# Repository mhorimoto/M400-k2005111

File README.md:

# 音声切り替え装置 (A26)
# K2005111

# 要求するHardware

- Arduino Nano V3
- 8ch Relay module
- I2C LCD 1602A (Address:0x27)

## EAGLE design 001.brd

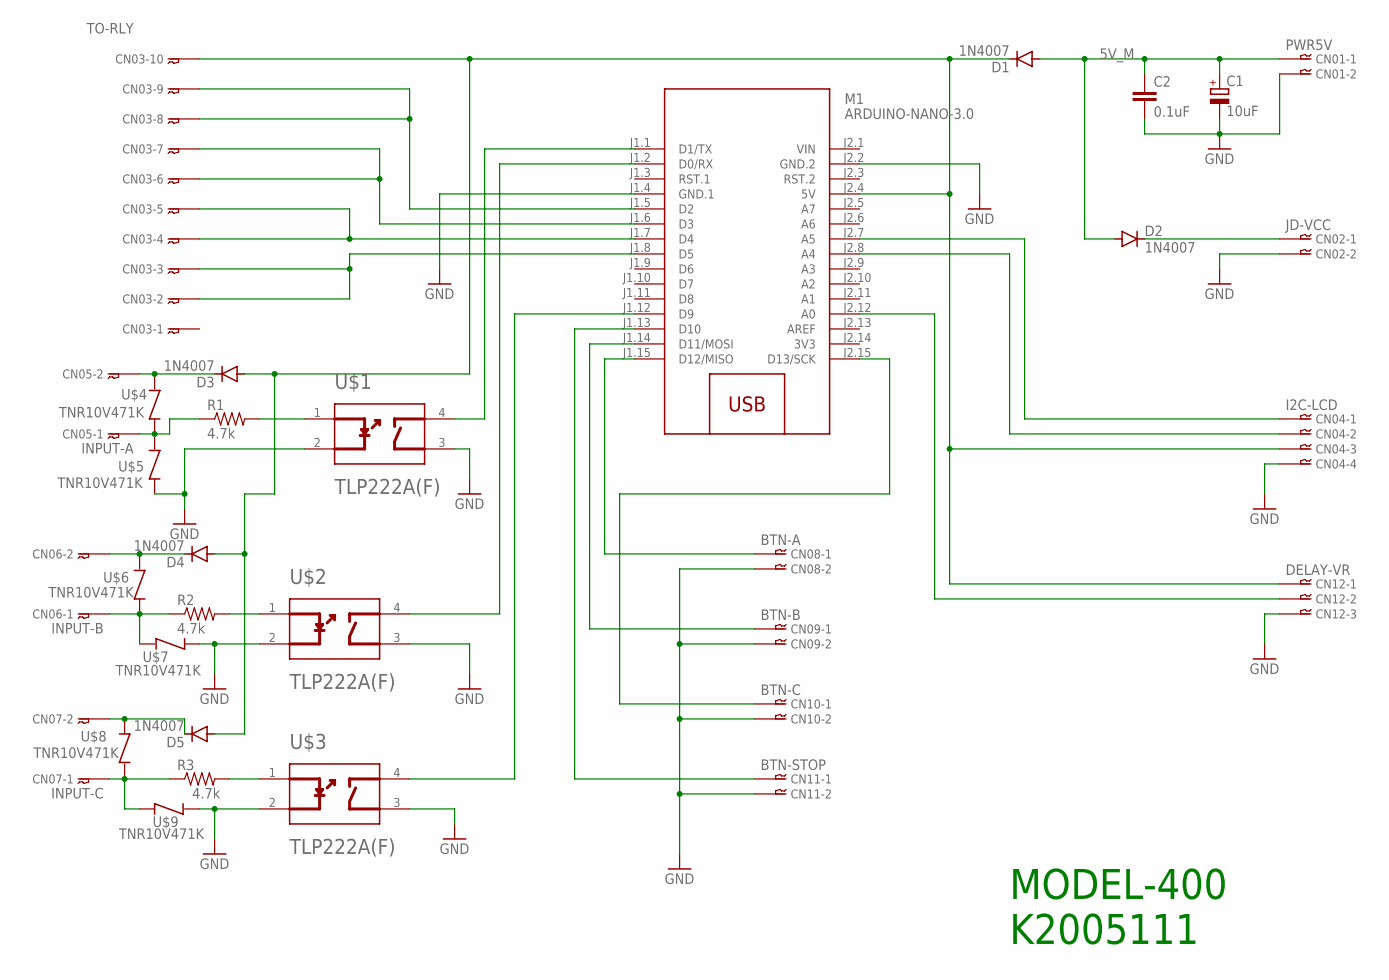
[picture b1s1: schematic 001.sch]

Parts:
C1: 10uF; E2-5
C2: 0.1uF; C025-025X050
CN01: PWR5V; B02B-XH
CN02: JD-VCC; B02B-XH
CN03: TO-RLY; B10B-XH
CN04: I2C-LCD; B04B-XH
CN05: INPUT-A; B02B-XH
CN06: INPUT-B; B02B-XH
CN07: INPUT-C; B02B-XH
CN08: BTN-A; B02B-XH
CN09: BTN-B; B02B-XH
CN10: BTN-C; B02B-XH
CN11: BTN-STOP; B02B-XH
CN12: DELAY-VR; B03B-XH
D1, D2, D3, D4, D5: 1N4007; DO41-10
M1: ARDUINO-NANO-3.0
R1, R2, R3: 4.7k; 0207/7
U$1: U1; TOSHIBA_TLP222A_F_0
U$2, U$3: TOSHIBA_TLP222A_F_SIMPLE; TOSHIBA_TLP222A_F_0
U$4, U$5, U$6, U$7, U$8, U$9: TNR10V471K; 08-043X78_VARI

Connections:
3V3: M1.J2.14 (3V3)
5V: CN03.P$10, CN04.P$3, CN12.P$1, D1.C, D3.A, D4.A, D5.A, M1.J2.4 (5V)
5V_B: CN02.P$1, D2.C
5V_M: C1.+, C2.1, CN01.P$1, D1.A, D2.A
GND: C1.-, C2.2, CN01.P$2, CN02.P$2, CN04.P$4, CN08.P$2, CN09.P$2, CN10.P$2, CN11.P$2, CN12.P$3, M1.J1.4 (GND.1), M1.J2.2 (GND.2), U$1.2 (CATHODE), U$1.3 (1_DRAIN), U$2.2 (CATHODE), U$2.3 (1_DRAIN), U$3.2 (CATHODE), U$3.3 (1_DRAIN), U$5.2, U$7.2, U$9.1
unnamed: CN03.P$4, CN03.P$5, M1.J1.7 (D4)
unnamed: CN03.P$2, CN03.P$3, M1.J1.8 (D5)
unnamed: CN04.P$2, M1.J2.8 (A4)
unnamed: CN04.P$1, M1.J2.7 (A5)
unnamed: M1.J1.12 (D9), U$3.4 (2_DRAIN)
unnamed: CN07.P$1, R3.1, U$8.1, U$9.2
unnamed: R3.2, U$3.1 (ANODE)
unnamed: CN10.P$1, M1.J2.15 (D13/SCK)
unnamed: CN03.P$6, CN03.P$7, M1.J1.6 (D3)
unnamed: CN07.P$2, D5.C, U$8.2
unnamed: CN03.P$8, CN03.P$9, M1.J1.5 (D2)
unnamed: M1.J1.2 (D0/RX), U$2.4 (2_DRAIN)
unnamed: R1.2, U$1.1 (ANODE)
unnamed: M1.J1.1 (D1/TX), U$1.4 (2_DRAIN)
unnamed: R2.2, U$2.1 (ANODE)
unnamed: CN06.P$1, R2.1, U$6.2, U$7.1
unnamed: CN06.P$2, D4.C, U$6.1
unnamed: CN05.P$1, R1.1, U$4.2, U$5.1
unnamed: CN05.P$2, D3.C, U$4.1
unnamed: CN11.P$1, M1.J1.13 (D10)
unnamed: CN09.P$1, M1.J1.14 (D11/MOSI)
unnamed: CN08.P$1, M1.J1.15 (D12/MISO)
unnamed: CN12.P$2, M1.J2.12 (A0)
VIN: M1.J2.1 (VIN)

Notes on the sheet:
MODEL-400 K2005111

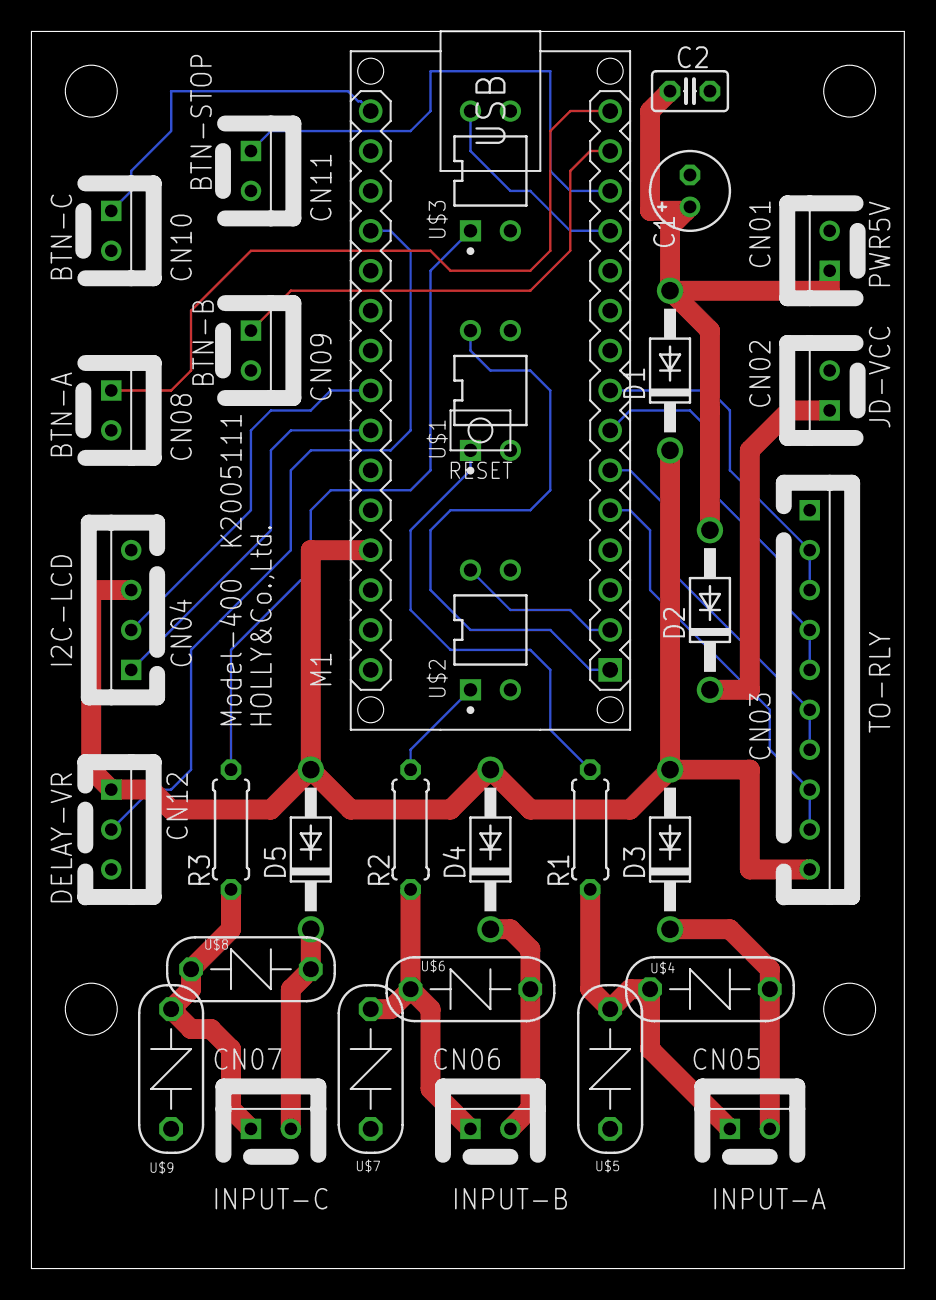
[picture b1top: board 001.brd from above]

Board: 2 copper layers, 55.5 x 78.7 mm, 32 parts (0 on the bottom side), 27 nets.

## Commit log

2020-06-15 1N4007に変更
2020-06-19 ソースコードと一緒に管理
2020-06-19 A11 Remote Mode中にSTOPボタンが効くようにする予定
2020-06-21 CAM初版
2020-06-22 ヴァリスタ追加
2020-06-25 KiCADへ移行
2020-06-26 foot printを見直し中
2020-06-27 ガーバーデータも出来た
2020-06-30 GBR初版
2020-07-19 fp-info-cacheが更新されてた
2020-07-19 Arduino IDEに合わせでプログラムを移動
2020-07-21 REMOTE MODEのinstsをswitch()する部分から
2020-07-22 program.ino途中
2020-07-22 A26版でほぼ完成。未検証
2020-07-24 PCBGOGOへ入稿
2020-07-27 GBR出し直し
2020-07-27 RS-274XでX2オプション外してドリル穴は１ファイル化
2020-08-08 フレームを追加とケースの加工データ
2020-08-31 VR取付支持台を作成
2020-09-01 A27 リリースかな。
2020-09-02 KiCAD用ignore file追加
2021-06-14 somthings
2021-06-15 debug:A28 remove serial operation

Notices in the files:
parts and their libraries:
diy-modules: Released under the Creative Commons Attribution 4.0 International License: http://creativecommons.org/licenses/by/4.0
